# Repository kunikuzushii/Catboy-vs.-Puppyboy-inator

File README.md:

# Catboy-vs.-Puppyboy-inator

Onshape Link : 

https://cad.onshape.com/documents/d6c669abeeb3d7413e8d21f8/w/bde522f027b95c0c69872acb/e/c43f71f52c280984713279bd?renderMode=0&uiState=6a39e0cea890183796429e63

____________________ 

A device that use a camera, machine learning, and hopes and dreams to detect if the registered faces are more likely to be a catboy or a puppyboy :D

# What is the Catboy vs. Puppboy Dectector?

It has:

- camera to capture your face
- buttons to scan your face
- an ML brain (hand-tuned facial-landmark math) ANNDD a trained image classifier voting together
- a screen that displays your verdict as a percentage
- RBG LED that shows you your results as a bonus

_____

#Why It Was Made? 

Well. There is no answer that I could give you that sounds professional or good enough in this readme other than the fact that I really enjoy guessing if people are cat-like or puppy-like. I technically play live furry-guesser with friends in public. 

I learned AI and machine learning in my AP CSA class and decided that yeah, my knowledge can be used to greater purposes such as this. I love making entertaining projects that gets a laugh out of people. 

(lowk im kinda into catboys yo)

# Pictures (☆▽☆)

CAD image:

PCB:

Live Scoring Demo (Application): 

## BILL OF MATERIALS

| Name | Qty | Unit | Price (USD) | Total (USD) | MOQ | MOQ Price | Source |
| :--- | :---: | :---: | ---: | ---: | :---: | ---: | :--- |
| Seeed XIAO ESP32S3 Sense (Pre-Soldered) | 1 | pcs | $14.90 | $14.90 | 1 | $14.90 | [Order](https://www.seeedstudio.com/Seeed-Studio-XIAO-ESP32S3-Sense-Pre-Soldered-p-6335.html) |
| Grove OLED Display 0.66" (SSD1306) | 1 | pcs | $5.50 | $5.50 | 1 | $5.50 | [Order](https://www.seeedstudio.com/Grove-OLED-Display-0-66-SSD1306-v1-0-p-5096.html) |
| TS-1187A-B-A-B Tactile Switch | 1 | pcs | $0.02 | $0.37 | 20 | $0.37 | [Order](https://www.lcsc.com/product-detail/C318884.html) |
| Adafruit NeoPixel Ring 12x5050 RGB LED | 1 | pcs | $8.95 | $8.95 | 1 | $8.95 | [Order](https://www.adafruit.com/product/1643) |
| Adafruit LiPo Battery 3.7V 500mAh | 1 | pcs | $7.95 | $7.95 | 1 | $7.95 | [Order](https://www.adafruit.com/product/1578) |
| JST S2B-PH-SM4-TB Battery Connector (SMD) | 1 | pcs | $0.12 | $0.12 | 1 | $0.12 | [Order](https://www.lcsc.com/product-detail/C295747.html) |
| PCB | 1 | pcs | $0.40 | $2.00 | 5 | $2.00 | [Order](https://jlcpcb.com) |
| PLA Housing | 1 | pcs | - | - | - | - | Self-Print / Local |
| M3 x 10mm Socket Cap Head Screws | 4 | pcs | $0.47 | $1.88 | 4 | $1.88 | [Order](https://accu-components.com/us/metric-cap-head-screws/16004-SSCF-M3-10-12-9) |
| M3 x 5mm Socket Cap Head Screws | 5 | pcs | $0.31 | $1.86 | 6 | $1.86 | [Order](https://accu-components.com/us/metric-cap-head-screws/16001-SSCF-M3-5-12-9) |

____

# BUILD & ASSEMBLY
___
# Required Tools
____
1) Soldering iron + solder
2) Tweezers
3) 3D Printer
4) Screwdriver for M3 screws
5) Computer with Arduino IDE + Python installed

# Assembly Directions:
______
1) Solder the ESP32C3. camera, buttons, LEDs, and battery onto the PCB following the schematic and layout
2) Check for incomplete connections
3) Mount the camera so it faces outward
4) Route the battery leads and place the LiPo into battery compartment. Check for polarity!
5) Align PCB into mounting posts then press it into place
6) Position top case onto the bottom case
7) Tighten screws into place
8) Install all the software libraries in Arduino
9) Set WiFi credentials and companion server IP at the top of the .ino sketch
10) Compile firmware and check for errors (shouldn't be any, if there is, check syntax for your edits)
11) On your laptop, start the companion Python server(python server.py). This runs the ML
12) Power on the device and press scan

After that confirm:
the display, results/score, battery life, wifi connection, wifi behavior, button, and LED

and then.. YOU'RE SET!

lmk if you're a catboy

# CREDITS:
- Onshape (for CAD)
- KiCad (schematic + PCB)
- MediaPipe (facial landmark extraction)
- Google Teachable Machine (classifier training)
Every friend who let us take a photo of their face for "science"

# DEPENDENCIES

Dependencies

You need these libraries (add via Arduino Library Manager):

- ArduinoJson (by Benoit Blanchon)
- WiFi (Built-in, ESP32 board package)
- HTTPClient (Built-in, ESP32 board package)
- (Built-in, ESP32 board package)
 
Python side (companion server):

- mediapipe
- opencv-python
- fastapi
- uvicorn
- numpy

# references
my big, beautiful brain for thinking of this idea.

and the catboys on pinterest

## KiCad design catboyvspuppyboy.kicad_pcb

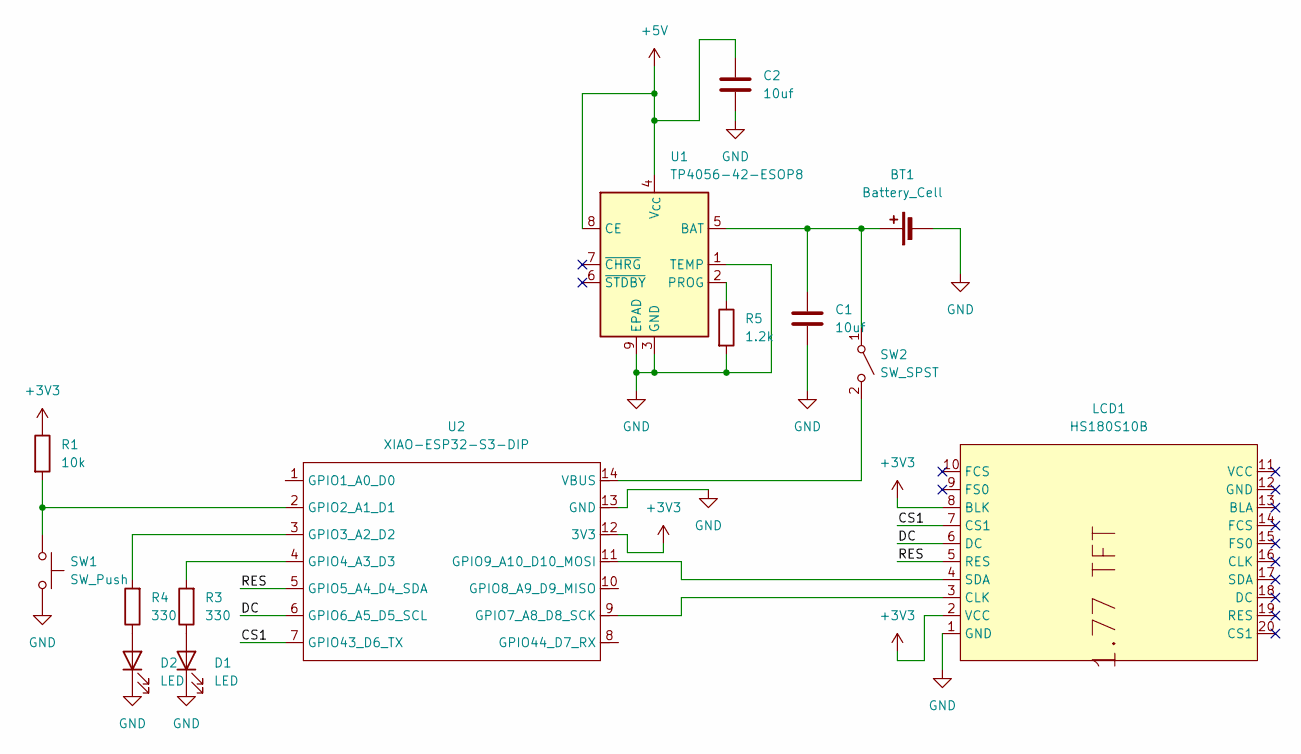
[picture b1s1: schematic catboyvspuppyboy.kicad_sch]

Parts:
BT1: Battery_Cell; JST_PH_S2B-PH-K_1x02_P2.00mm_Horizontal
C1, C2: 10uf; C_0805_2012Metric
D1, D2: LED; LED_0805_2012Metric
LCD1: HS180S10B; LCD-TH_L56.0-W35.0-P2.54_HS180S10B; MPN HS180S10B; LCSC Part C5329585
R1: 10k; R_0805_2012Metric
R3, R4: 330; R_0805_2012Metric
R5: 1.2k; R_0805_2012Metric
SW1: SW_Push; SW_PUSH_6mm_H5mm
SW2: SW_SPST; SW_Slide_SPDT_Straight_CK_OS102011MS2Q
U1: TP4056-42-ESOP8; SOIC-8-1EP_3.9x4.9mm_P1.27mm_EP2.41x3.3mm_ThermalVias
U2: XIAO-ESP32-S3-DIP; XIAO-ESP32-C3-DIP

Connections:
+3V3: LCD1.2 (VCC), LCD1.8 (BLK), R1.1, U2.12 (3V3)
+5V: C2.1, U1.4 (V_{CC}), U1.8 (CE)
/CS1: LCD1.7 (CS1), U2.7 (GPIO43_D6_TX)
/DC: LCD1.6 (DC), U2.6 (GPIO6_A5_D5_SCL)
/RES: LCD1.5 (RES), U2.5 (GPIO5_A4_D4_SDA)
GND: BT1.2 (-), C1.2, C2.2, D1.1 (K), D2.1 (K), LCD1.1 (GND), R5.2, SW1.2, U1.1 (TEMP), U1.3 (GND), U1.9 (EPAD), U2.13 (GND)
unnamed: BT1.1 (+), C1.1, SW2.1 (A), U1.5 (BAT)
unnamed: D1.2 (A), R3.1
unnamed: D2.2 (A), R4.1
unnamed: SW2.2 (B), U2.14 (VBUS)
unnamed: R5.1, U1.2 (PROG)
unnamed: R1.2, SW1.1, U2.2 (GPIO2_A1_D1)
unnamed: R4.2, U2.3 (GPIO3_A2_D2)
unnamed: R3.2, U2.4 (GPIO4_A3_D3)
unnamed: LCD1.3 (CLK), U2.9 (GPIO7_A8_D8_SCK)
unnamed: LCD1.4 (SDA), U2.11 (GPIO9_A10_D10_MOSI)

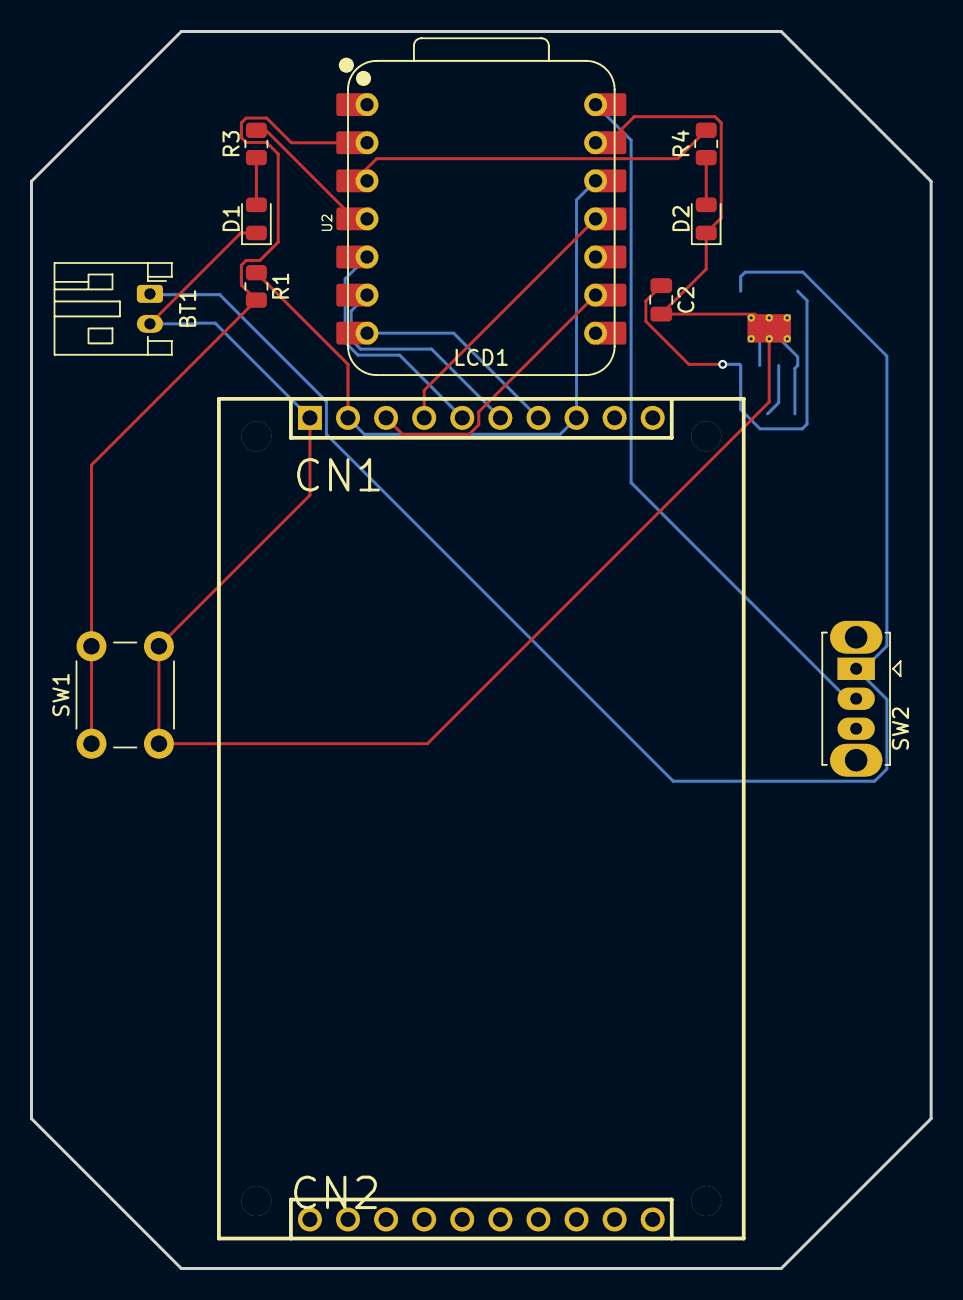
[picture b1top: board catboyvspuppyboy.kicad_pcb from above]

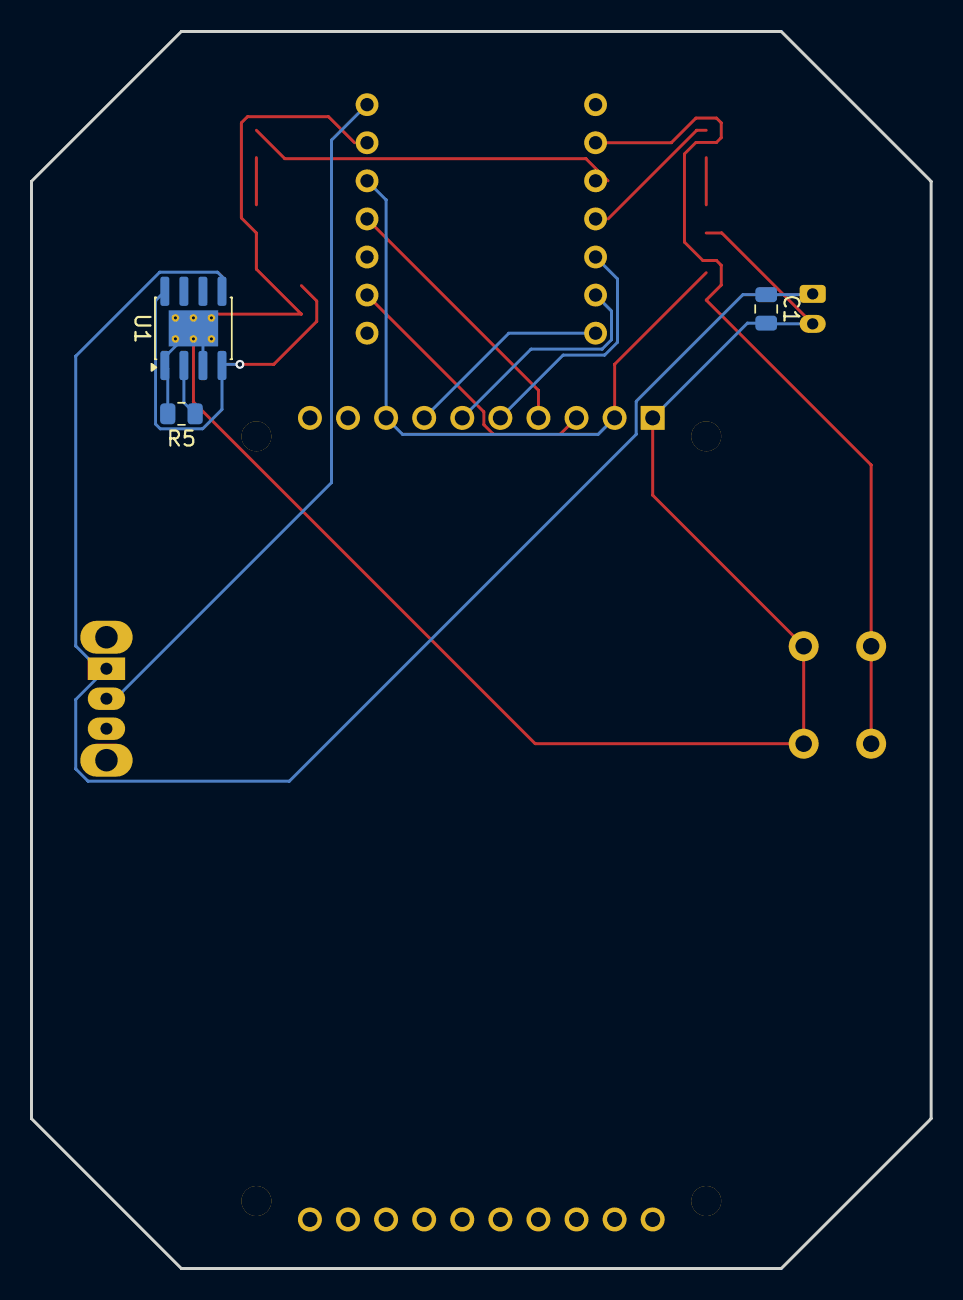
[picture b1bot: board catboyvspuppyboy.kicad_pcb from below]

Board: 2 copper layers, 60.0 x 82.5 mm, 14 parts (3 on the bottom side), 16 nets.
